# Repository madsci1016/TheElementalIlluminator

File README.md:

TheElementalIlluminator
=======================

An Arduino sketch for a Periodic Display that has an LED strip behind each element. The hardware uses TLC5940s to control the LEDs. See http://www.billporter.info/?p=1750

/******************************************************************
*  Dan's Perodic Table Display
*	 By Bill Porter
*		details:
*	        	http://www.billporter.info/?p=1750
*
*
*	 Contributers:
*		Just me so far
*
*  Version history
*    1.0 Tested working 

*
*
*This program is free software: you can redistribute it and/or modify 
it under the terms of the GNU General Public License as published by the 
Free Software Foundation, either version 3 of the License, or(at your option) any later version.
This program is distributed in the hope that it will be useful,
but WITHOUT ANY WARRANTY; without even the implied warranty of
MERCHANTABILITY or FITNESS FOR A PARTICULAR PURPOSE.  See the
GNU General Public License for more details.
<http://www.gnu.org/licenses/>

*This work is licensed under the Creative Commons Attribution-ShareAlike 3.0 Unported License. 
*To view a copy of this license, visit http://creativecommons.org/licenses/by-sa/3.0/ or
*send a letter to Creative Commons, 444 Castro Street, Suite 900, Mountain View, California, 94041, USA.
*  
******************************************************************/

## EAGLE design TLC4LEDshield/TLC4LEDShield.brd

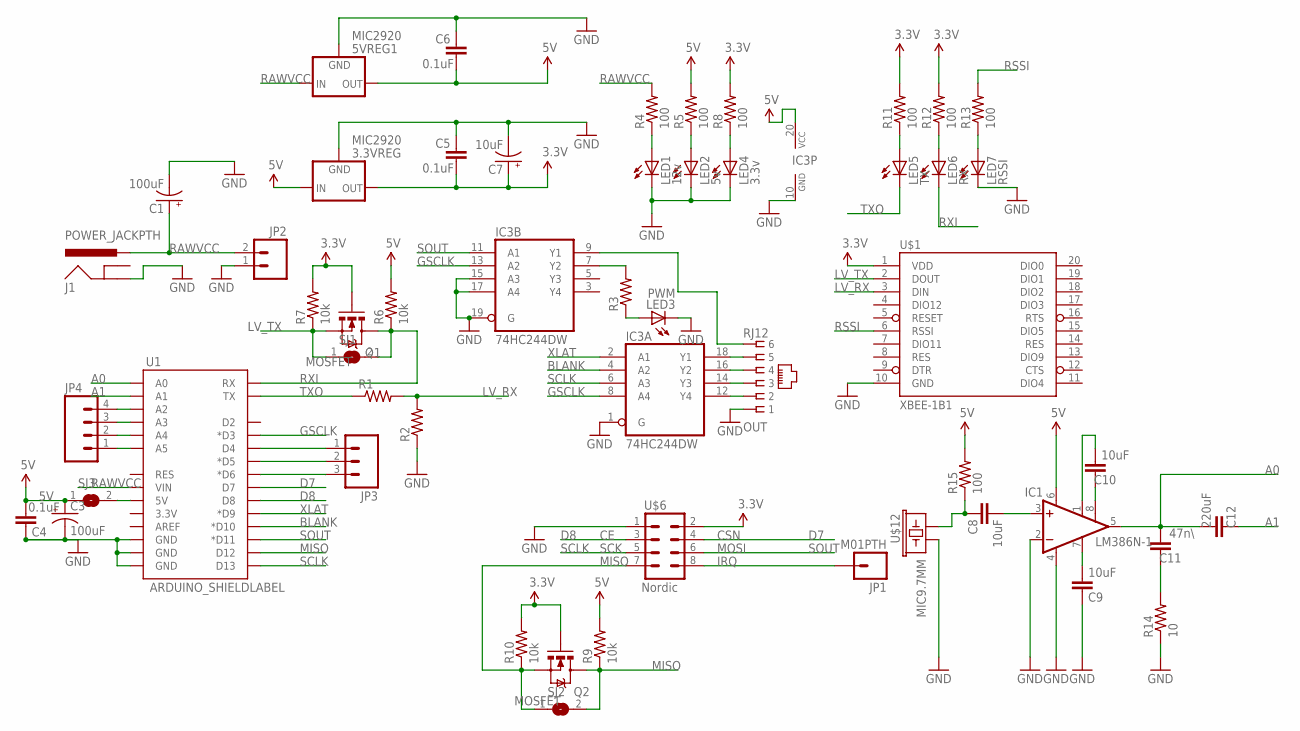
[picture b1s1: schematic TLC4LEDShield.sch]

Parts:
3.3VREG, 5VREG1: MIC2920; SOT223
C1, C3: 100uF; PANASONIC_D
C4, C5, C6: 0.1uF; 0805
C7: 10uF; EIA3216
C8, C9, C10: 10uF; 0805
C11: 47n\; 0805
C12: 220uF; 0805
IC1: LM386N-1; DIL08
IC3: 74HC244DW; SO20W
J1: POWER_JACKPTH; POWER_JACK_PTH
JP1: M01PTH; 1X01
JP2: M025MM; SCREWTERMINAL-5MM-2
JP3: M03PTH; 1X03
JP4: M04PTH; 1X04
LED1: 12v; CHIPLED_0805
LED2: 5v; CHIPLED_0805
LED3: PWM; CHIPLED_0805
LED4: 3.3v; CHIPLED_0805
LED5: TX; CHIPLED_0805
LED6: RX; CHIPLED_0805
LED7: RSSI; CHIPLED_0805
OUT: RJ12; RJ11-NO_SHIELD; MPN RJ11-6L-B
Q1, Q2: MOSFET; SOT23-3
R1, R2: RESISTOR0805-RES; 0805
R3: R-US_R0805; R0805
R4, R5, R8, R11, R12, R13, R15: 100; 0805
R6, R7, R9, R10: 10k; 0805
R14: 10; 0805
SJ1, SJ2, SJ3: SJ
U1: ARDUINO_SHIELDLABEL; DUEMILANOVE_SHIELD
U$1: XBEE-1B1; XBEE-1
U$6: Nordic; 2X4
U$12: MIC9.7MM; MIC-9.7MM

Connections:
3.3V: 3.3VREG.3 (OUT), C5.1, C7.A (+), Q1.1 (G), Q2.1 (G), R7.2, R8.2, R10.2, R11.2, R12.2, U$1.1 (VDD), U$6.2
5V: 3.3VREG.1 (IN), 5VREG1.3 (OUT), C3.+, C4.1, C6.1, IC1.6 (VS), IC3.20 (VCC), R5.2, R6.2, R9.2, R15.2, SJ3.1
A0: C11.1, C12.1, IC1.5 (OUT), U1.A0
A1: C12.2, U1.A1
BLANK: IC3.4 (A2), U1.D10 (*D10)
D7: U1.D7, U$6.4
D8: U1.D8, U$6.3
GND: 3.3VREG.2 (GND), 5VREG1.2 (GND), C1.-, C3.-, C4.2, C5.2, C6.2, C7.C (-), C9.2, IC1.2 (-IN), IC1.4 (GND), IC3.1 (G), IC3.10 (GND), IC3.15 (A3), IC3.17 (A4), IC3.19 (G), J1.GND, JP2.1, LED1.C, LED2.C, LED3.C, LED4.C, LED7.C, OUT.1, R2.1, R14.1, U1.GND@0 (GND), U1.GND@1 (GND), U1.GND@2 (GND), U$1.10 (GND), U$6.1, U$12.2
GSCLK: IC3.8 (A4), IC3.13 (A2), U1.D3 (*D3)
LV_RX: R1.2, R2.2, U$1.3 (DIN)
LV_TX: Q1.2 (S), R7.1, SJ1.1, U$1.2 (DOUT)
MISO: Q2.3 (D), R9.1, SJ2.2, U1.D12
unnamed: IC3.12 (Y4), OUT.2
unnamed: IC3.14 (Y3), OUT.3
unnamed: IC3.16 (Y2), OUT.4
unnamed: IC3.18 (Y1), OUT.5
unnamed: LED2.A, R5.1
unnamed: LED1.A, R4.1
unnamed: LED5.A, R11.1
unnamed: LED6.A, R12.1
unnamed: Q2.2 (S), R10.1, SJ2.1, U$6.7
unnamed: LED7.A, R13.1
unnamed: SJ3.2, U1.5V
unnamed: JP1.1, U$6.8
unnamed: LED4.A, R8.1
unnamed: JP3.1, U1.D4
unnamed: JP3.2, U1.D5 (*D5)
unnamed: JP3.3, U1.D6 (*D6)
unnamed: JP4.1, U1.A5
unnamed: IC3.9 (Y1), OUT.6
unnamed: JP4.2, U1.A4
unnamed: IC3.7 (Y2), R3.2
unnamed: LED3.A, R3.1
unnamed: JP4.3, U1.A3
unnamed: JP4.4, U1.A2
unnamed: C8.1, IC1.3 (+IN)
unnamed: C9.1, IC1.7 (BYPASS)
unnamed: C10.2, IC1.8 (GAIN)
unnamed: C10.1, IC1.1 (GAIN)
unnamed: C11.2, R14.2
unnamed: C8.2, R15.1, U$12.1
RAWVCC: 5VREG1.1 (IN), C1.+, J1.PWR, JP2.2, R4.2, U1.VIN
RSSI: R13.2, U$1.6 (RSSI)
RXI: LED6.C, Q1.3 (D), R6.1, SJ1.2, U1.RX
SCLK: IC3.6 (A3), U1.D13, U$6.5
SOUT: IC3.11 (A1), U1.D11 (*D11), U$6.6
TXO: LED5.C, R1.1, U1.TX
XLAT: IC3.2 (A1), U1.D9 (*D9)

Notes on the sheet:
CSN
SCK
MOSI
MISO
IRQ

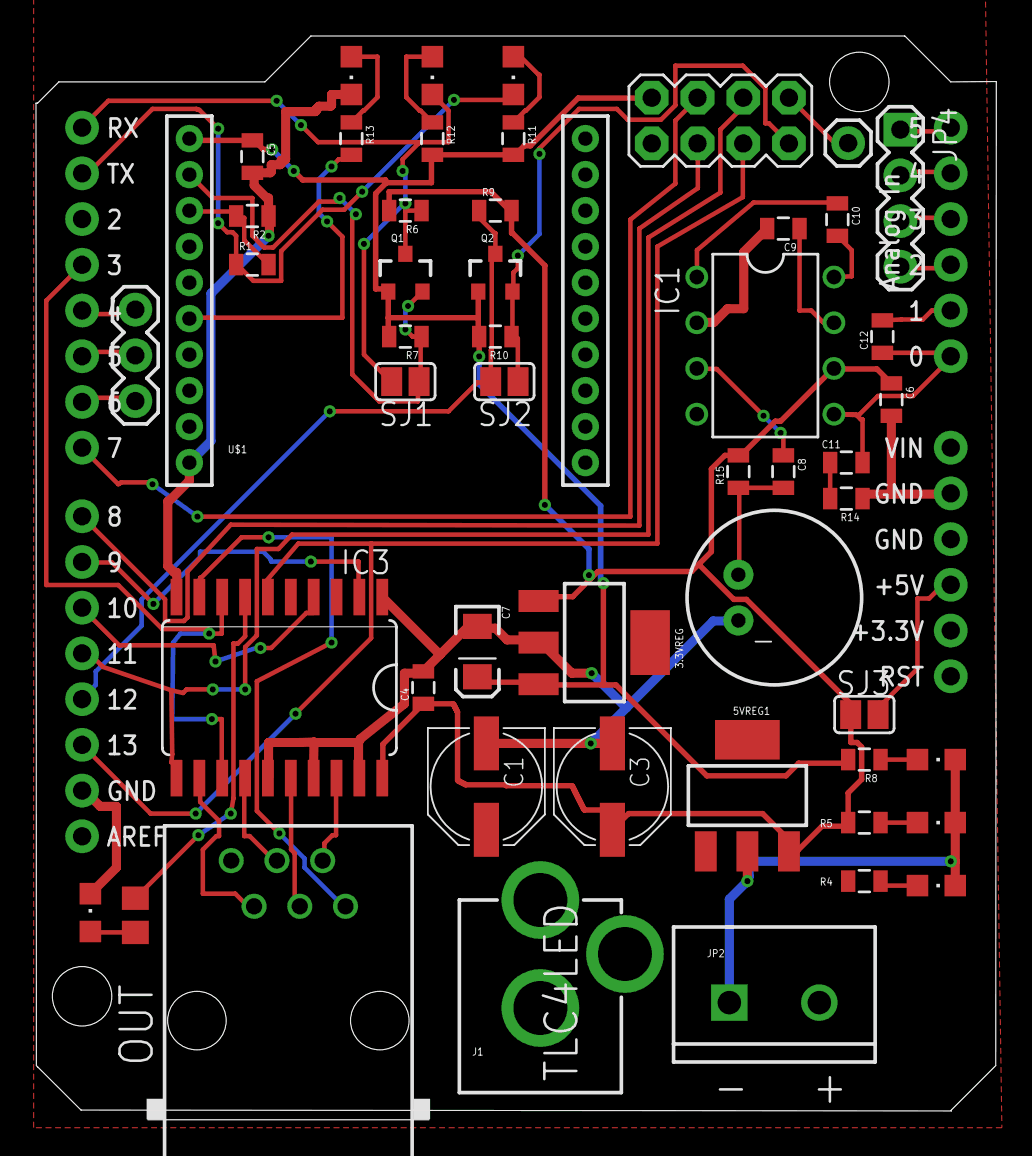
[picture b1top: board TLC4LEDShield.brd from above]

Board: 2 copper layers, 53.3 x 60.2 mm, 52 parts (0 on the bottom side), 48 nets.

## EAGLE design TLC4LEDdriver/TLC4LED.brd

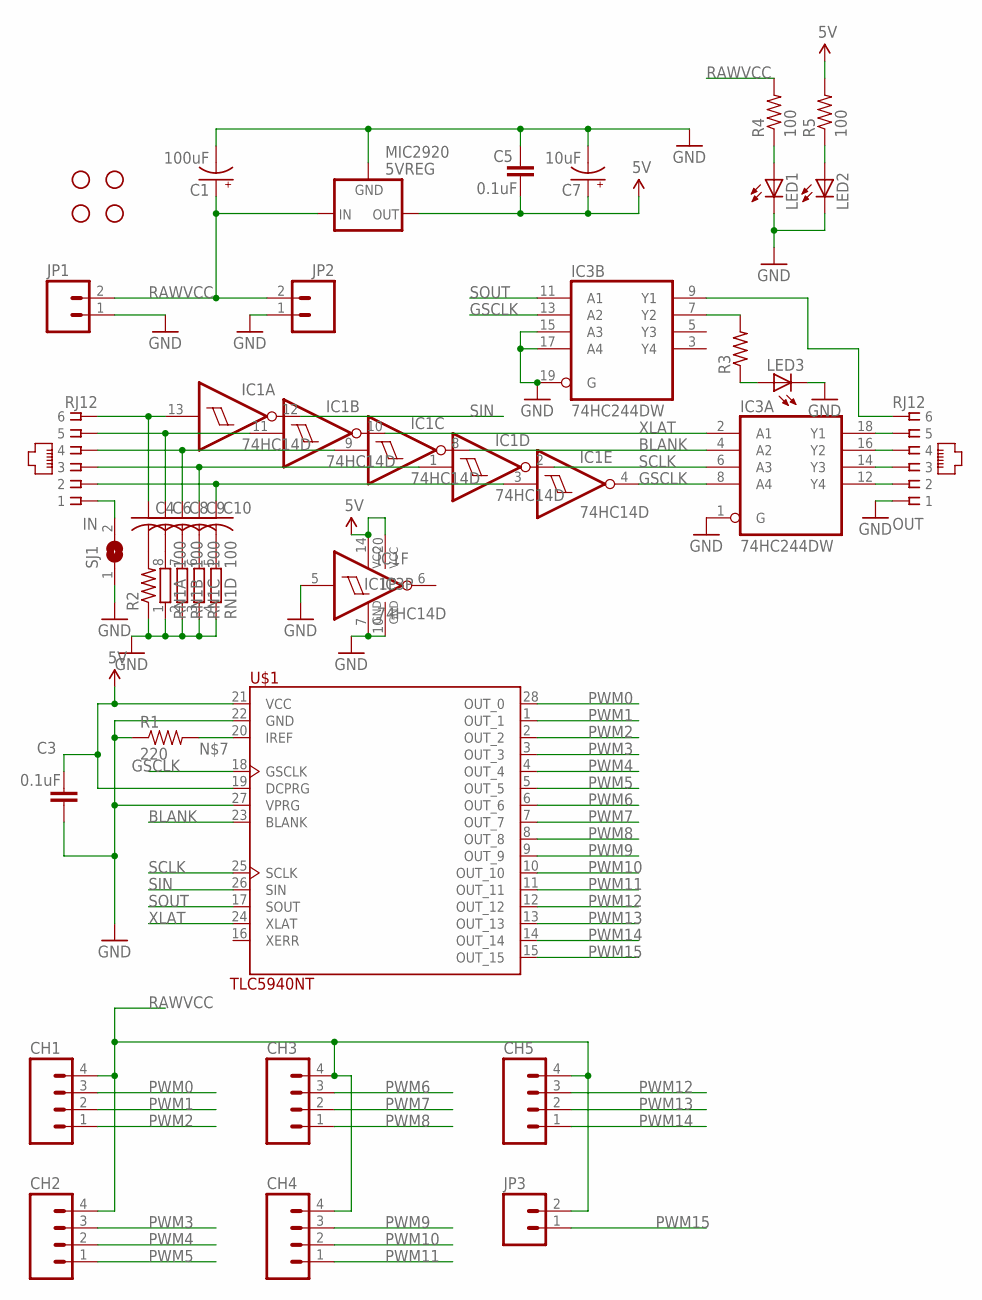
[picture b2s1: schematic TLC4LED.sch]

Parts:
5VREG: MIC2920; SOT223
C1: 100uF; PANASONIC_D
C3, C5: 0.1uF; 0805
C4, C6, C8, C9, C10: C-US025-025X050; C025-025X050
C7: 10uF; EIA3216
CH1, CH2, CH3, CH4, CH5: M04SCREW; SCREWTERMINAL-3.5MM-4
IC1: 74HC14D; SO14
IC3: 74HC244DW; SO20W
IN: RJ12; RJ11-NO_SHIELD
JP1, JP2, JP3: M023.5MM; SCREWTERMINAL-3.5MM-2
JP4, JP5, JP6, JP7: STAND-OFF
LED1, LED2, LED3: LEDCHIPLED_0805; CHIPLED_0805
OUT: RJ12; RJ11-NO_SHIELD; MPN RJ11-6L-B
R1: 220; 0805
R2, R3: R-US_R0805; R0805
R4, R5: 100; 0805
RN1: 100; EXBS8V
SJ1: SJ
U$1: TLC5940NT; DIP-28

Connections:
5V: 5VREG.3 (OUT), C3.2, C5.1, C7.A (+), IC1.14 (VCC), IC3.20 (VCC), R5.2, U$1.19 (DCPRG), U$1.21 (VCC)
BLANK: IC1.8 (O), IC3.4 (A2), U$1.23 (BLANK)
GND: 5VREG.2 (GND), C1.-, C3.1, C5.2, C7.C (-), IC1.5 (I), IC1.7 (GND), IC3.1 (G), IC3.10 (GND), IC3.15 (A3), IC3.17 (A4), IC3.19 (G), JP1.1, JP2.1, LED1.C, LED2.C, LED3.C, OUT.1, R1.1, R2.1, RN1.1, RN1.2 (1), RN1.3 (1), RN1.4 (1), SJ1.1, U$1.22 (GND), U$1.27 (VPRG)
GSCLK: IC1.4 (O), IC3.8 (A4), IC3.13 (A2), U$1.18 (GSCLK)
unnamed: IC3.12 (Y4), OUT.2
unnamed: IC3.14 (Y3), OUT.3
unnamed: IC3.16 (Y2), OUT.4
unnamed: IC3.18 (Y1), OUT.5
unnamed: LED2.A, R5.1
unnamed: LED1.A, R4.1
unnamed: R1.2, U$1.20 (IREF)
unnamed: C4.1, IC1.13 (I), IN.6
unnamed: C6.1, IC1.11 (I), IN.5
unnamed: C8.1, IC1.9 (I), IN.4
unnamed: C10.2, RN1.5 (2)
unnamed: C9.2, RN1.6 (2)
unnamed: C8.2, RN1.7 (2)
unnamed: C9.1, IC1.1 (I), IN.3
unnamed: C10.1, IC1.3 (I), IN.2
unnamed: C6.2, RN1.8 (2)
unnamed: C4.2, R2.2
unnamed: IC3.9 (Y1), OUT.6
unnamed: IN.1, SJ1.2
unnamed: IC3.7 (Y2), R3.2
unnamed: LED3.A, R3.1
PWM0: CH1.3, U$1.28 (OUT_0)
PWM1: CH1.2, U$1.1 (OUT_1)
PWM2: CH1.1, U$1.2 (OUT_2)
PWM3: CH2.3, U$1.3 (OUT_3)
PWM4: CH2.2, U$1.4 (OUT_4)
PWM5: CH2.1, U$1.5 (OUT_5)
PWM6: CH3.3, U$1.6 (OUT_6)
PWM7: CH3.2, U$1.7 (OUT_7)
PWM8: CH3.1, U$1.8 (OUT_8)
PWM9: CH4.3, U$1.9 (OUT_9)
PWM10: CH4.2, U$1.10 (OUT_10)
PWM11: CH4.1, U$1.11 (OUT_11)
PWM12: CH5.3, U$1.12 (OUT_12)
PWM13: CH5.2, U$1.13 (OUT_13)
PWM14: CH5.1, U$1.14 (OUT_14)
PWM15: JP3.1, U$1.15 (OUT_15)
RAWVCC: 5VREG.1 (IN), C1.+, CH1.4, CH2.4, CH3.4, CH4.4, CH5.4, JP1.2, JP2.2, JP3.2, R4.2
SCLK: IC1.2 (O), IC3.6 (A3), U$1.25 (SCLK)
SIN: IC1.12 (O), U$1.26 (SIN)
SOUT: IC3.11 (A1), U$1.17 (SOUT)
XLAT: IC1.10 (O), IC3.2 (A1), U$1.24 (XLAT)

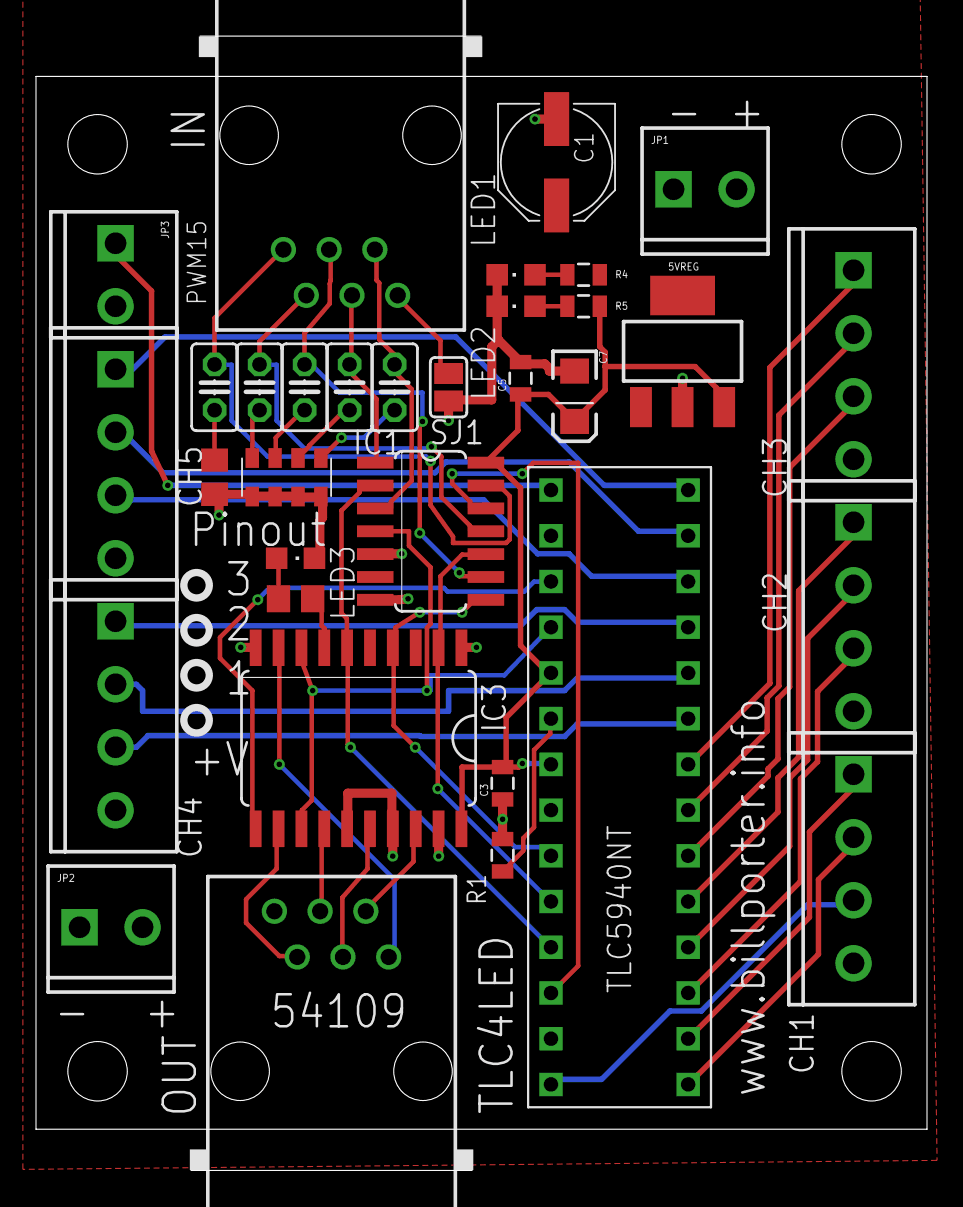
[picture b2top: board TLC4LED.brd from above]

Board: 2 copper layers, 49.5 x 63.0 mm, 37 parts (0 on the bottom side), 46 nets.

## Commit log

2013-02-03 Added Board SRCs and BOM
